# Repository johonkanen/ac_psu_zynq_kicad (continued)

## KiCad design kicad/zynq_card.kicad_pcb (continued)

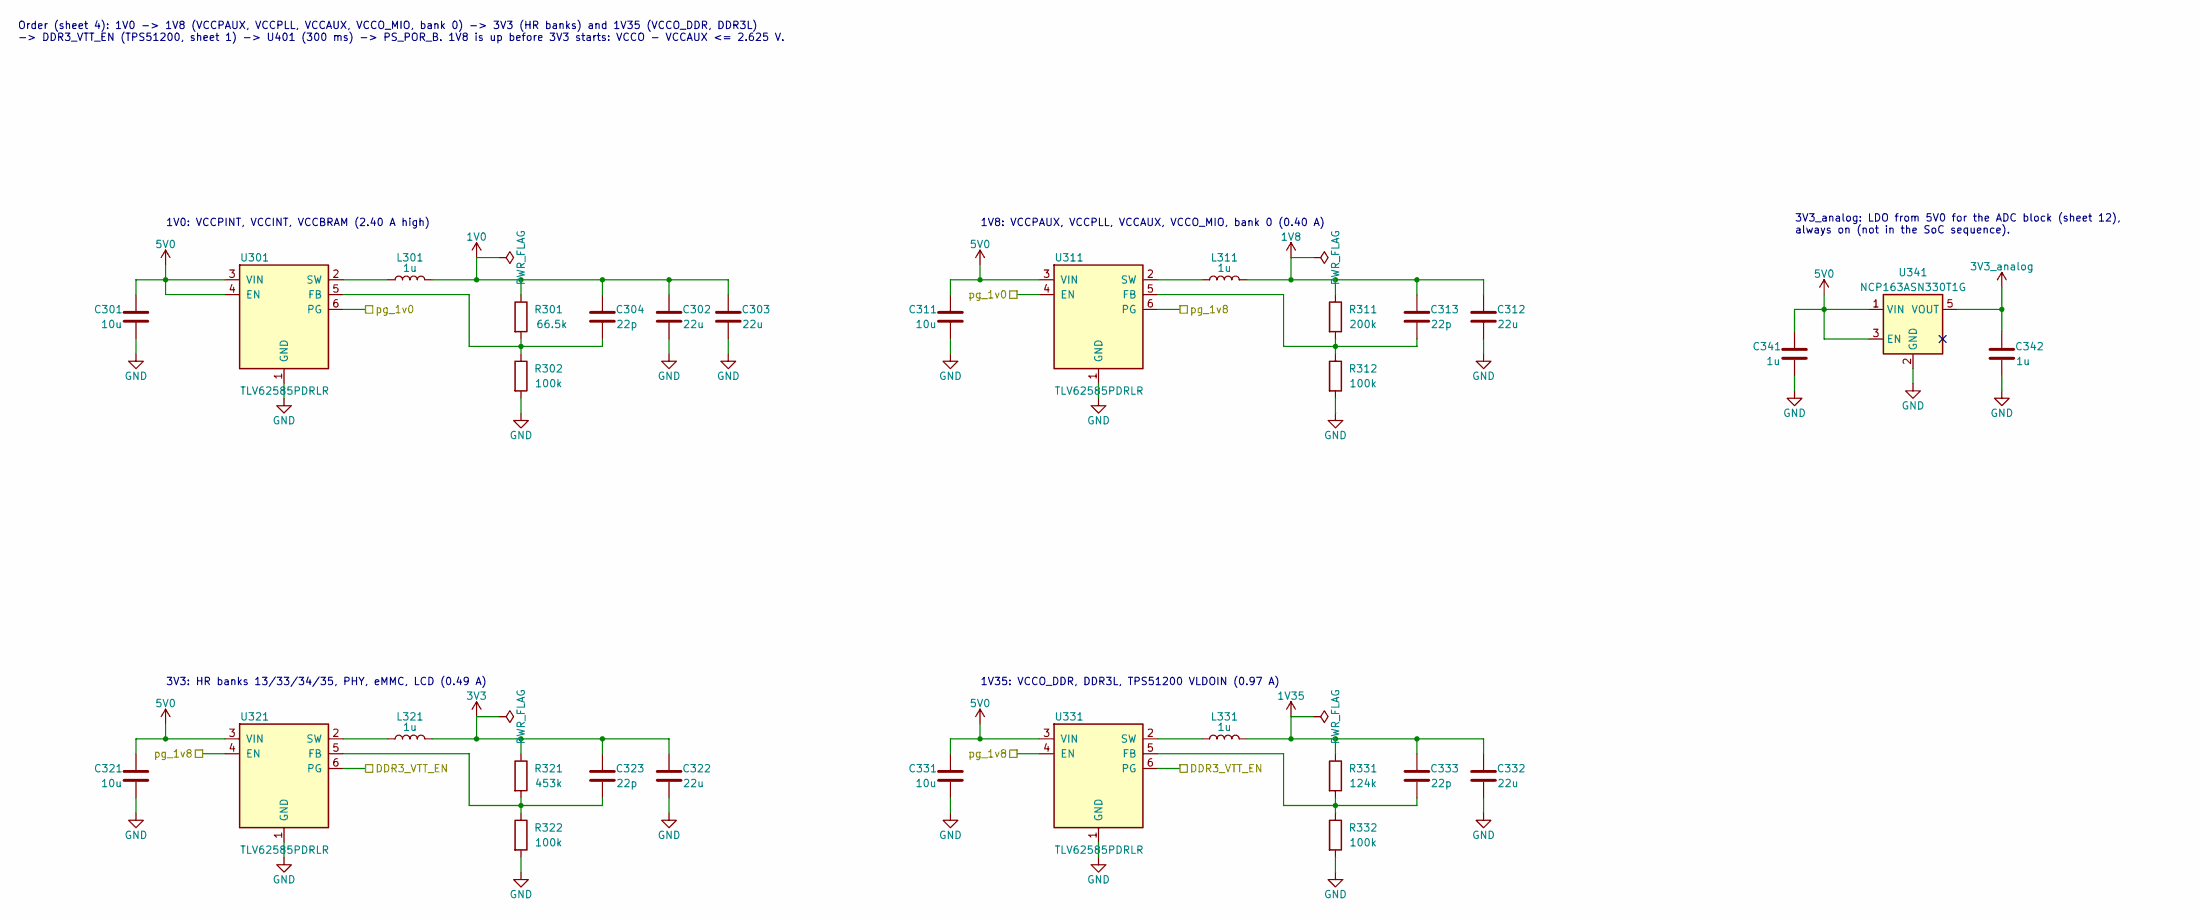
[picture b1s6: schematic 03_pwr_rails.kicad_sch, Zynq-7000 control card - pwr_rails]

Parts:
C301, C311, C321, C331: 10u; C_0805_2012Metric; LCSC C15850
C302, C303, C312, C322, C332: 22u; C_0805_2012Metric; LCSC C45783
C304, C313, C323, C333: 22p; C_0402_1005Metric; LCSC C1555
C341, C342: 1u; C_0402_1005Metric; LCSC C52923
L301, L311, L321, L331: 1u; L_Coilcraft_XxL4020; MPN WPN4020H1R0MT; LCSC C98359
R301: 66.5k; R_0402_1005Metric; LCSC C2998095
R302, R312, R322, R332: 100k; R_0402_1005Metric; LCSC C25741
R311: 200k; R_0402_1005Metric; LCSC C25764
R321: 453k; R_0402_1005Metric; LCSC C27009
R331: 124k; R_0402_1005Metric; LCSC C2933070
U301, U311, U321, U331: TLV62585PDRLR; SOT-563; LCSC C485118
U341: NCP163ASN330T1G; SOT-23-5; LCSC C603656

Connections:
1V0: C302.1, C303.1, C304.1, L301.2, R301.1; also elsewhere on the board
1V8: C312.1, C313.1, L311.2, R311.1; also elsewhere on the board
1V35: C332.1, C333.1, L331.2, R331.1; also elsewhere on the board
3V3: C322.1, C323.1, L321.2, R321.1; also elsewhere on the board
3V3_analog: C342.1, U341.5 (VOUT); also elsewhere on the board
5V0: C301.1, C311.1, C321.1, C331.1, C341.1, U301.3 (VIN), U301.4 (EN), U311.3 (VIN), U321.3 (VIN), U331.3 (VIN), U341.1 (VIN), U341.3 (EN); also elsewhere on the board
/DDR3_VTT_EN: U321.6 (PG), U331.6 (PG); also elsewhere on the board
/pg_1v0: U301.6 (PG), U311.4 (EN); also elsewhere on the board
/pg_1v8: U311.6 (PG), U321.4 (EN), U331.4 (EN); also elsewhere on the board
GND: C301.2, C302.2, C303.2, C311.2, C312.2, C321.2, C322.2, C331.2, C332.2, C341.2, C342.2, R302.2, R312.2, R322.2, R332.2, U301.1 (GND), U311.1 (GND), U321.1 (GND), U331.1 (GND), U341.2 (GND); also elsewhere on the board
unnamed: C304.2, R301.2, R302.1, U301.5 (FB)
unnamed: L301.1, U301.2 (SW)
unnamed: C313.2, R311.2, R312.1, U311.5 (FB)
unnamed: L311.1, U311.2 (SW)
unnamed: C323.2, R321.2, R322.1, U321.5 (FB)
unnamed: L321.1, U321.2 (SW)
unnamed: C333.2, R331.2, R332.1, U331.5 (FB)
unnamed: L331.1, U331.2 (SW)

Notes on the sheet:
Order (sheet 4): 1V0 -> 1V8 (VCCPAUX, VCCPLL, VCCAUX, VCCO_MIO, bank 0) -> 3V3 (HR banks) and 1V35 (VCCO_DDR, DDR3L) -> DDR3_VTT_EN (TPS51200, sheet 1) -> U401 (300 ms) -> PS_POR_B. 1V8 is up before 3V3 starts: VCCO - VCCAUX <= 2.625 V.
1V0: VCCPINT, VCCINT, VCCBRAM (2.40 A high)
1V8: VCCPAUX, VCCPLL, VCCAUX, VCCO_MIO, bank 0 (0.40 A)
3V3: HR banks 13/33/34/35, PHY, eMMC, LCD (0.49 A)
1V35: VCCO_DDR, DDR3L, TPS51200 VLDOIN (0.97 A)
3V3_analog: LDO from 5V0 for the ADC block (sheet 12), always on (not in the SoC sequence).

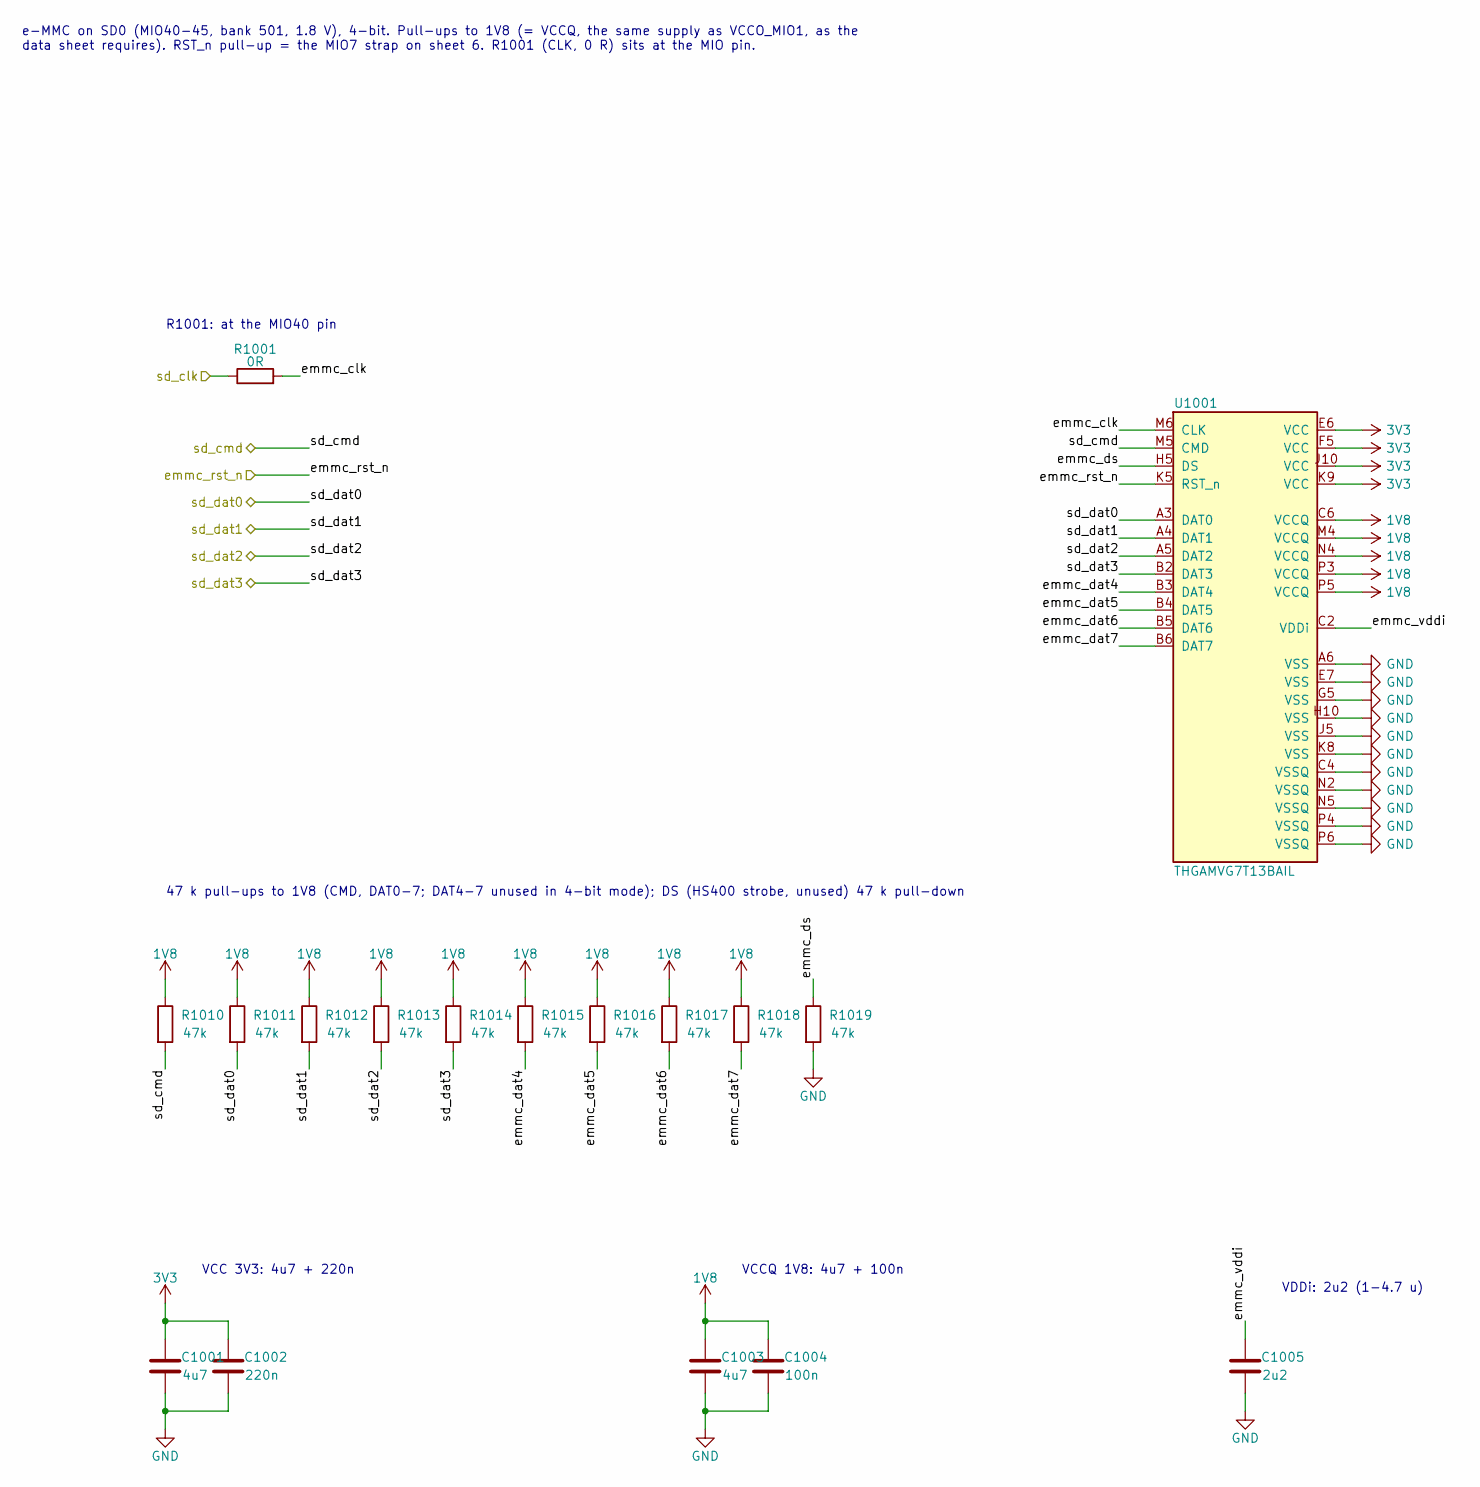
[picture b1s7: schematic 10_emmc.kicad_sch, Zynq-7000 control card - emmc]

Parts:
C1001, C1003: 4u7; C_0402_1005Metric; LCSC C23733
C1002: 220n; C_0402_1005Metric; LCSC C16772
C1004: 100n; C_0402_1005Metric; LCSC C1525
C1005: 2u2; C_0402_1005Metric; LCSC C12530
R1001: 0R; R_0402_1005Metric; LCSC C17168
R1010, R1011, R1012, R1013, R1014, R1015, R1016, R1017, R1018, R1019: 47k; R_0402_1005Metric; LCSC C25792
U1001: THGAMVG7T13BAIL; LFBGA-153_11.5x13mm_Layout14x14_P0.5mm; LCSC C7599693

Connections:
1V8: C1003.1, C1004.1, R1010.1, R1011.1, R1012.1, R1013.1, R1014.1, R1015.1, R1016.1, R1017.1, R1018.1, U1001.C6 (VCCQ), U1001.M4 (VCCQ), U1001.N4 (VCCQ), U1001.P3 (VCCQ), U1001.P5 (VCCQ); also elsewhere on the board
3V3: C1001.1, C1002.1, U1001.E6 (VCC), U1001.F5 (VCC), U1001.J10 (VCC), U1001.K9 (VCC); also elsewhere on the board
/10 emmc/emmc_clk: R1001.2, U1001.M6 (CLK)
/10 emmc/emmc_dat4: R1015.2, U1001.B3 (DAT4)
/10 emmc/emmc_dat5: R1016.2, U1001.B4 (DAT5)
/10 emmc/emmc_dat6: R1017.2, U1001.B5 (DAT6)
/10 emmc/emmc_dat7: R1018.2, U1001.B6 (DAT7)
/10 emmc/emmc_ds: R1019.1, U1001.H5 (DS)
/10 emmc/emmc_vddi: C1005.1, U1001.C2 (VDDi)
/emmc_rst_n: U1001.K5 (RST_n); also elsewhere on the board
/sd_clk: R1001.1; also elsewhere on the board
/sd_cmd: R1010.2, U1001.M5 (CMD); also elsewhere on the board
/sd_dat0: R1011.2, U1001.A3 (DAT0); also elsewhere on the board
/sd_dat1: R1012.2, U1001.A4 (DAT1); also elsewhere on the board
/sd_dat2: R1013.2, U1001.A5 (DAT2); also elsewhere on the board
/sd_dat3: R1014.2, U1001.B2 (DAT3); also elsewhere on the board
GND: C1001.2, C1002.2, C1003.2, C1004.2, C1005.2, R1019.2, U1001.A6 (VSS), U1001.C4 (VSSQ), U1001.E7 (VSS), U1001.G5 (VSS), U1001.H10 (VSS), U1001.J5 (VSS), U1001.K8 (VSS), U1001.N2 (VSSQ), U1001.N5 (VSSQ), U1001.P4 (VSSQ), U1001.P6 (VSSQ); also elsewhere on the board

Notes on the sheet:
e-MMC on SD0 (MIO40-45, bank 501, 1.8 V), 4-bit. Pull-ups to 1V8 (= VCCQ, the same supply as VCCO_MIO1, as the data sheet requires). RST_n pull-up = the MIO7 strap on sheet 6. R1001 (CLK, 0 R) sits at the MIO pin.
R1001: at the MIO40 pin
47 k pull-ups to 1V8 (CMD, DAT0-7; DAT4-7 unused in 4-bit mode); DS (HS400 strobe, unused) 47 k pull-down
VCC 3V3: 4u7 + 220n
VCCQ 1V8: 4u7 + 100n
VDDi: 2u2 (1-4.7 u)

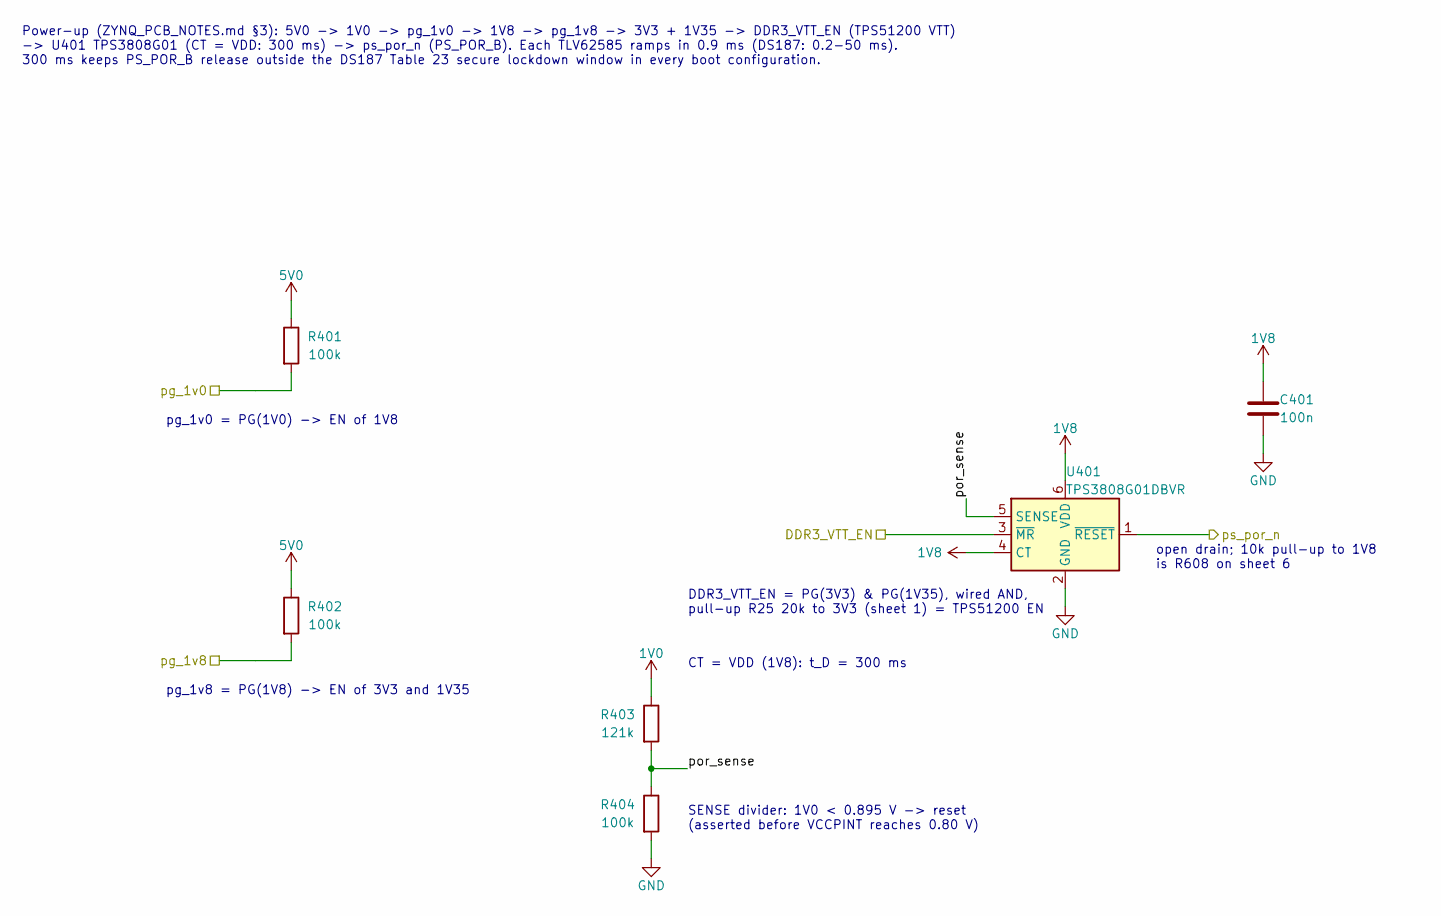
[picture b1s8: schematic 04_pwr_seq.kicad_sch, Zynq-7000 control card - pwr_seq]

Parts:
C401: 100n; C_0402_1005Metric; LCSC C1525
R401, R402, R404: 100k; R_0402_1005Metric; LCSC C25741
R403: 121k; R_0402_1005Metric; LCSC C11693
U401: TPS3808G01DBVR; SOT-23-6; MPN TPS3808G01DBVR; LCSC C19653

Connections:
1V0: R403.1; also elsewhere on the board
1V8: C401.1, U401.4 (CT), U401.6 (VDD); also elsewhere on the board
5V0: R401.1, R402.1; also elsewhere on the board
/04 pwr_seq/por_sense: R403.2, R404.1, U401.5 (SENSE)
/DDR3_VTT_EN: U401.3 (~MR); also elsewhere on the board
/pg_1v0: R401.2; also elsewhere on the board
/pg_1v8: R402.2; also elsewhere on the board
/ps_por_n: U401.1 (~RESET); also elsewhere on the board
GND: C401.2, R404.2, U401.2 (GND); also elsewhere on the board

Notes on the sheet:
Power-up (ZYNQ_PCB_NOTES.md §3): 5V0 -> 1V0 -> pg_1v0 -> 1V8 -> pg_1v8 -> 3V3 + 1V35 -> DDR3_VTT_EN (TPS51200 VTT) -> U401 TPS3808G01 (CT = VDD: 300 ms) -> ps_por_n (PS_POR_B). Each TLV62585 ramps in 0.9 ms (DS187: 0.2-50 ms). 300 ms keeps PS_POR_B release outside the DS187 Table 23 secure lockdown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
pg_1v0 = PG(1V0) -> EN of 1V8
pg_1v8 = PG(1V8) -> EN of 3V3 and 1V35
DDR3_VTT_EN = PG(3V3) & PG(1V35), wired AND, pull-up R25 20k to 3V3 (sheet 1) = TPS51200 EN
CT = VDD (1V8): t_D = 300 ms
SENSE divider: 1V0 < 0.895 V -> reset (asserted before VCCPINT reaches 0.80 V)
open drain; 10k pull-up to 1V8 is R608 on sheet 6

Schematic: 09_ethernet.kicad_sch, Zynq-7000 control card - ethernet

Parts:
C901, C921, C922, C931, C932, C933, C934, C936, C941, C950, C951: 100n; C_0402_1005Metric; LCSC C1525
C910, C911: 27p; C_0402_1005Metric; LCSC C107002
C920: 10u; C_0805_2012Metric; LCSC C15850
C930, C935, C940: 1u; C_0402_1005Metric; LCSC C52923
FB901: BLM15PX121SN1D; L_0402_1005Metric; LCSC C88970
J9: HR911130A; RJ45_Hanrun_HR911130A_Horizontal; LCSC C54408
R901, R902, R903, R904, R905, R906, R907, R908, R909, R910, R911, R912: 22R; R_0402_1005Metric; LCSC C25092
R920, R921, R922, R923, R924, R925, R926, R927, R928, R929, R930: 4k7; R_0402_1005Metric; LCSC C25900
R931: 2.49k 1%; R_0402_1005Metric; LCSC C25884
R932: 10k; R_0402_1005Metric; LCSC C25744
R933: 1k; R_0402_1005Metric; LCSC C11702
R950: 330R; R_0402_1005Metric; LCSC C25104
U901: RTL8211FDI-CG; QFN-40-1EP_5x5mm_P0.4mm_EP3.6x3.6mm_ThermalVias; LCSC C692886
U902: 74LVC1G07GW; SOT-353_SC-70-5; LCSC C282345
Y901: 25MHz; Crystal_SMD_3225-4Pin_3.2x2.5mm; MPN X322525MRB4SI; LCSC C70593

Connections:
1V8: C951.1, R929.1, R930.1, U902.5 (VCC); also elsewhere on the board
3V3: C940.1, C941.1, FB901.1, R928.1, R932.1, R950.1, U901.29 (DVDD33); also elsewhere on the board
/09 ethernet/eth_ct: C950.1, J9.1 (TCT)
/09 ethernet/eth_led_a: J9.11 (LEDG_A), R950.2
/09 ethernet/eth_led_k: J9.12 (LEDG_K), R928.2, U901.34 (LED2/CFG_LDO1)
/09 ethernet/eth_mdi_a_N: J9.3 (MDI0-), U901.2 (MDIN0)
/09 ethernet/eth_mdi_a_P: J9.2 (MDI0+), U901.1 (MDIP0)
/09 ethernet/eth_mdi_b_N: J9.7 (MDI1-), U901.5 (MDIN1)
/09 ethernet/eth_mdi_b_P: J9.4 (MDI1+), U901.4 (MDIP1)
/09 ethernet/eth_mdi_c_N: J9.6 (MDI2-), U901.7 (MDIN2)
/09 ethernet/eth_mdi_c_P: J9.5 (MDI2+), U901.6 (MDIP2)
/09 ethernet/eth_mdi_d_N: J9.9 (MDI3-), U901.10 (MDIN3)
/09 ethernet/eth_mdi_d_P: J9.8 (MDI3+), U901.9 (MDIP3)
/09 ethernet/phy_avdd33: C920.1, C921.1, C922.1, FB901.2, U901.11 (AVDD33), U901.40 (AVDD33)
/09 ethernet/phy_dvdd_rg: C935.1, C936.1, R920.1, R925.1, U901.28 (DVDD_RG)
/09 ethernet/phy_led0: R926.1, U901.32 (LED0/CFG_EXT)
/09 ethernet/phy_led1: R927.1, U901.33 (LED1/CFG_LDO0)
/09 ethernet/phy_rset: R931.1, U901.39 (RSET)
/09 ethernet/phy_rstb: C901.1, R932.2, U901.12 (PHYRSTB), U902.4
/09 ethernet/phy_rx_ctl: R908.2, R922.1, U901.26 (RXCTL/PHYAD2)
/09 ethernet/phy_rxc: R907.2, R921.1, U901.27 (RXC/PHYAD1)
/09 ethernet/phy_rxd0: R909.2, R925.2, U901.25 (RXD0/RXDLY)
/09 ethernet/phy_rxd1: R910.2, R924.1, U901.24 (RXD1/TXDLY)
/09 ethernet/phy_rxd2: R911.2, R923.1, U901.23 (RXD2/PLLOFF)
/09 ethernet/phy_rxd3: R912.2, R920.2, U901.22 (RXD3/PHYAD0)
/09 ethernet/phy_tx_ctl: R902.2, U901.19 (TXCTL)
/09 ethernet/phy_txc: R901.2, U901.20 (TXC)
/09 ethernet/phy_txd0: R903.2, U901.18 (TXD0)
/09 ethernet/phy_txd1: R904.2, U901.17 (TXD1)
/09 ethernet/phy_txd2: R905.2, U901.16 (TXD2)
/09 ethernet/phy_txd3: R906.2, U901.15 (TXD3)
/09 ethernet/phy_vdd10: C930.1, C931.1, C932.1, C933.1, C934.1, U901.3 (AVDD10), U901.8 (AVDD10), U901.21 (DVDD10), U901.30 (LDO_OUT), U901.38 (AVDD10)
/09 ethernet/phy_xi: C910.1, U901.36 (XTAL_IN), Y901.1
/09 ethernet/phy_xo: C911.1, U901.37 (XTAL_OUT), Y901.3
/eth_int_n: R930.2, U901.31 (INTB/PMEB); also elsewhere on the board
/eth_rst_n: R933.1, U902.2; also elsewhere on the board
/mdc: U901.13 (MDC); also elsewhere on the board
/mdio: R929.2, U901.14 (MDIO); also elsewhere on the board
/rgmii_rx_ctl: R908.1; also elsewhere on the board
/rgmii_rxc: R907.1; also elsewhere on the board
/rgmii_rxd0: R909.1; also elsewhere on the board
/rgmii_rxd1: R910.1; also elsewhere on the board
/rgmii_rxd2: R911.1; also elsewhere on the board
/rgmii_rxd3: R912.1; also elsewhere on the board
/rgmii_tx_ctl: R902.1; also elsewhere on the board
/rgmii_txc: R901.1; also elsewhere on the board
/rgmii_txd0: R903.1; also elsewhere on the board
/rgmii_txd1: R904.1; also elsewhere on the board
/rgmii_txd2: R905.1; also elsewhere on the board
/rgmii_txd3: R906.1; also elsewhere on the board
GND: C901.2, C910.2, C911.2, C920.2, C921.2, C922.2, C930.2, C931.2, C932.2, C933.2, C934.2, C935.2, C936.2, C940.2, C941.2, C950.2, C951.2, J9.10 (CHS), J9.SH (SHIELD), R921.2, R922.2, R923.2, R924.2, R926.2, R927.2, R931.2, R933.2, U901.41 (GND), U902.3 (GND), Y901.2 (G), Y901.4 (G); also elsewhere on the board

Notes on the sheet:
RTL8211FDI-CG gigabit PHY, RGMII at 1.8 V (internal pad LDO) to GEM0 (MIO16-27, bank 501), MDIO0 on MIO52/53, PHY address 1. 3.3 V only: core 1.0 V from its own LDO. J9 = HanRun HR911130A magjack (green LED from LED2, yellow spare), placed per MECHANICAL.md.
RGMII series 22 R: TX at the SoC (MIO), RX at the PHY (source side)
Straps 4k7: PHYAD = 001 (RXD3 up, RXC/RXCTL down), PLLOFF/TXDLY = 0, RXDLY = 1 (RX pins to DVDD_RG); CFG_EXT = 0 (LED0 down), CFG_LDO = 10 (LED1 down, LED2 up to 3V3) -> 1.8 V RGMII pads. MDIO/INT_N pull-ups to 1V8.
PHYRSTB is a 3.3 V input: U902 74LVC1G07 (1V8 supply) open drain, R932 10k to 3V3, C901 filter. R933 1k holds eth_rst_n (MIO9) low against the MIO reset pull-up until software releases the PHY.
25 MHz crystal 3225, 27 p load (Agilex card values), +/-50 ppm total; place at the PHY
AVDD33 (pins 11, 40) through a ferrite: 10u + 2 x 100n
LDO_OUT 1.0 V -> AVDD10 (3, 8, 38) + DVDD10 (21) only: 1u + 4 x 100n (>= 0.1u, Table 9.2)
DVDD_RG: RGMII pad LDO output (1.8 V), caps only
DVDD33 (pin 29)
Jack LED: green anode via R950 to 3V3, cathode on PHY LED2 (3.3 V pin, active low with its CFG_LDO1 pull-up R928). Program LCR for link/activity.

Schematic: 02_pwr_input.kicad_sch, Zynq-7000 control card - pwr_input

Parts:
C201: 47u; C_1206_3216Metric; LCSC C96123
C202: 22u; C_0805_2012Metric; LCSC C45783
C203: 100n; C_0402_1005Metric; LCSC C1525
J6: 2x3 1.27mm (bottom); PinSocket_2x03_P1.27mm_Vertical

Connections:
5V0: C201.1, C202.1, C203.1, J6.2, J6.4, J6.6; also elsewhere on the board
GND: C201.2, C202.2, C203.2, J6.1, J6.3, J6.5; also elsewhere on the board

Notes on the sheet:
J6 = baseboard J12 (2x3 1.27 mm socket on B.Cu, MECHANICAL.md): 5V0 = baseboard 5V_ISOL, GND = ISOGND. Supply budget: POWER_BUDGET.md (0.89 A typ / 1.44 A high; needs the baseboard U8 upgrade to 1.5-2 A).
GND: the card's only ground (baseboard ISOGND)
Input bulk at J6 (the regulators have their own 10u).

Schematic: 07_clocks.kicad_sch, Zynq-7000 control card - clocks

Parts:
C701: 470n; C_0402_1005Metric; LCSC C47339
FB701: BLM18PG121SN1D; L_0603_1608Metric; MPN BLM18PG121SN1D; LCSC C14709
R701: 33; R_0402_1005Metric; LCSC C25105
Y701: 33.333MHz; Oscillator_SMD_Abracon_ASE-4Pin_3.2x2.5mm; MPN OT322533.3333MJBA4SL; LCSC C2831392

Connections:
1V8: FB701.1; also elsewhere on the board
/07 clocks/osc_vdd: C701.1, FB701.2, Y701.1 (EN), Y701.4 (Vdd)
/ps_clk: R701.2; also elsewhere on the board
GND: C701.2, Y701.2 (GND); also elsewhere on the board
unnamed: R701.1, Y701.3 (OUT)

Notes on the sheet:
PS_CLK: Y701 33.333 MHz, 1.8 V CMOS (bank 500 = VCCO_MIO0 = 1.8 V) -> R701 33 R at Y701 -> ps_clk (U20 F7). Circuit of the Agilex 3 card's oscillator: EN tied to VDD, supply through FB701 with C701 470 n. Layout: Y701 close to F7, one point-to-point trace, R701 at the oscillator pin.

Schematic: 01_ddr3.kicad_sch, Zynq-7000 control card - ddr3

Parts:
C93, C98, C105, C106, C109, C110: .01uF; C_0402_1005Metric; MPN CL05B103KB5NNNC; LCSC C15195
C94, C95, C96, C97, C131: .1uF; C_0402_1005Metric; MPN CL05B104KO5NNNC; LCSC C1525
C99: 100uF; C_1210_3225Metric; MPN CL32A107MQVNNNE; LCSC C49066
C100, C127: 4.7uF; C_0402_1005Metric; MPN CL05A475MP5NRNC; LCSC C23733
C101, C102, C103, C104: .47uF; C_0402_1005Metric; MPN CL05A474KP5NNNC; LCSC C47339
C125, C126, C128, C129, C130: 10uF; C_0603_1608Metric; MPN CL10A106KP8NNNC; LCSC C19702
D7: BLUE LED; C_0603_1608Metric; MPN VLMB1300-GS08; LCSC C435849
R25: 20k; R_0402_1005Metric; MPN RT0402BRD0720KL; LCSC C705630
R46, R49: 240 1%; R_0402_1005Metric; MPN RC0402FR-07240RL; LCSC C114755
R47, R48: 10k 1%; R_0402_1005Metric; MPN 0402WGF1002TCE; LCSC C25744
R50, R75, R76: 80.6 1%; R_0402_1005Metric; MPN RC0402FR-0780R6L; LCSC C185392
R51, R52, R53, R54, R55, R56, R57, R58, R59, R60, R61, R62, R63, R64, R65, R66, R67, R68, R69, R70, R71, R72, R73: 40.2 1%; R_0402_1005Metric; MPN RC0402FR-0740R2L; LCSC C274892
R74: 4.7k; R_0402_1005Metric; MPN 0402WGF4701TCE; LCSC C25900
R101: 100k; R_0402_1005Metric; MPN 0402WGF1003TCE; LCSC C25741
R102: 150; R_0402_1005Metric; MPN RC-02K1500FT; LCSC C140202
U8: TPS51200DRCR; VSON-10-1EP_3x3mm_P0.5mm_EP1.65x2.4mm_ThermalVias; MPN TPS51200DRCR; LCSC C34771
U15, U16: MT41K256M16TW-107:P; FBGA-96-DDR3-SDRAM; MPN MT41K256M16TW-107:P; LCSC C253882
U20: XC7Z020-2CLG484I; BGA-484_19.0x19.0mm_Layout22x22_P0.80mm_dia0.40mm; MPN XC7Z020-2CLG484I; LCSC C157624

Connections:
1V35: C94.1, C96.1, C99.1, C100.1, C101.1, C102.1, C103.1, C104.1, C109.1, C110.1, C125.1, C126.1, R47.1, R75.2, U8.2 (VLDOIN), U15.A1 (VDDQ), U15.A8 (VDDQ), U15.B2 (VDD), U15.C1 (VDDQ), U15.C9 (VDDQ), U15.D2 (VDDQ), U15.D9 (VDD), U15.E9 (VDDQ), U15.F1 (VDDQ), U15.G7 (VDD), U15.H2 (VDDQ), U15.H9 (VDDQ), U15.K2 (VDD), U15.K8 (VDD), U15.N1 (VDD), U15.N9 (VDD), U15.R1 (VDD), U15.R9 (VDD), U16.A1 (VDDQ), U16.A8 (VDDQ), U16.B2 (VDD), U16.C1 (VDDQ), U16.C9 (VDDQ), U16.D2 (VDDQ), U16.D9 (VDD), U16.E9 (VDDQ), U16.F1 (VDDQ), U16.G7 (VDD), U16.H2 (VDDQ), U16.H9 (VDDQ), U16.K2 (VDD), U16.K8 (VDD), U16.N1 (VDD), U16.N9 (VDD), U16.R1 (VDD), U16.R9 (VDD), U20.E2 (VCCO_DDR_502[9]), U20.F5 (VCCO_DDR_502[9]), U20.H1 (VCCO_DDR_502[9]), U20.J4 (VCCO_DDR_502[9]), U20.K7 (VCCO_DDR_502[9]), U20.M3 (VCCO_DDR_502[9]), U20.N6 (VCCO_DDR_502[9]), U20.R2 (VCCO_DDR_502[9]), U20.V1 (VCCO_DDR_502[9]); also elsewhere on the board
3V3: C127.2, R25.1, R101.1, R102.2, U8.10 (VIN); also elsewhere on the board
/01 ddr3/PGOOD_LED: D7.2 (A), R102.1
/01 ddr3/VREF: C93.1, C94.2, C95.1, C96.2, C97.1, C98.1, C105.1, C106.1, R47.2, R48.1, U8.1 (REFIN), U15.H1 (VREFDQ), U15.M8 (VREFCA), U16.H1 (VREFDQ), U16.M8 (VREFCA), U20.H7 (PS_DDR_VREF0_502), U20.P7 (PS_DDR_VREF1_502)
/01 ddr3/ZQH: R46.1, U15.L8 (ZQ)
/01 ddr3/ZQL: R49.1, U16.L8 (ZQ)
/DDR3_VTT_EN: R25.2, U8.7 (EN); also elsewhere on the board
DDR3_A0: R51.1, U15.N3 (A0), U16.N3 (A0), U20.M4 (PS_DDR_A0_502)
DDR3_A1: R52.1, U15.P7 (A1), U16.P7 (A1), U20.M5 (PS_DDR_A1_502)
DDR3_A2: R53.1, U15.P3 (A2), U16.P3 (A2), U20.K4 (PS_DDR_A2_502)
DDR3_A3: R54.1, U15.N2 (A3), U16.N2 (A3), U20.L4 (PS_DDR_A3_502)
DDR3_A4: R55.1, U15.P8 (A4), U16.P8 (A4), U20.K6 (PS_DDR_A4_502)
DDR3_A5: R56.1, U15.P2 (A5), U16.P2 (A5), U20.K5 (PS_DDR_A5_502)
DDR3_A6: R57.1, U15.R8 (A6), U16.R8 (A6), U20.J7 (PS_DDR_A6_502)
DDR3_A7: R58.1, U15.R2 (A7), U16.R2 (A7), U20.J6 (PS_DDR_A7_502)
DDR3_A8: R59.1, U15.T8 (A8), U16.T8 (A8), U20.J5 (PS_DDR_A8_502)
DDR3_A9: R60.1, U15.R3 (A9), U16.R3 (A9), U20.H5 (PS_DDR_A9_502)
DDR3_A10: R61.1, U15.L7 (A10/AP), U16.L7 (A10/AP), U20.J3 (PS_DDR_A10_502)
DDR3_A11: R62.1, U15.R7 (A11), U16.R7 (A11), U20.G5 (PS_DDR_A11_502)
DDR3_A12: R63.1, U15.N7 (A12/!BC), U16.N7 (A12/!BC), U20.H4 (PS_DDR_A12_502)
DDR3_A13: R64.1, U15.T3 (A13), U16.T3 (A13), U20.F4 (PS_DDR_A13_502)
DDR3_A14: R65.1, U15.T7 (A14), U16.T7 (A14), U20.G4 (PS_DDR_A14_502)
DDR3_BA0: R66.1, U15.M2 (BA0), U16.M2 (BA0), U20.L7 (PS_DDR_BA0_502)
DDR3_BA1: R67.1, U15.N8 (BA1), U16.N8 (BA1), U20.L6 (PS_DDR_BA1_502)
DDR3_BA2: R68.1, U15.M3 (BA2), U16.M3 (BA2), U20.M6 (PS_DDR_BA2_502)
DDR3_CAS#: R70.1, U15.K3 (~CAS), U16.K3 (~CAS), U20.P3 (PS_DDR_CAS_B_502)
DDR3_CKE: U15.K9 (CKE), U16.K9 (CKE), U20.V3 (PS_DDR_CKE_502)
DDR3_CK_N: R50.2, U15.K7 (~CK), U16.K7 (~CK), U20.N5 (PS_DDR_CKN_502)
DDR3_CK_P: R50.1, U15.J7 (CK), U16.J7 (CK), U20.N4 (PS_DDR_CKP_502)
DDR3_CS#: R73.1, U15.L2 (~CS), U16.L2 (~CS), U20.P6 (PS_DDR_CS_B_502)
DDR3_DM0: U16.E7 (LDM), U20.B1 (PS_DDR_DM0_502)
DDR3_DM1: U16.D3 (UDM), U20.H3 (PS_DDR_DM1_502)
DDR3_DM2: U15.E7 (LDM), U20.P1 (PS_DDR_DM2_502)
DDR3_DM3: U15.D3 (UDM), U20.AA2 (PS_DDR_DM3_502)
DDR3_DQ0: U16.E3 (DQ0), U20.C3 (PS_DDR_DQ1_502)
DDR3_DQ1: U16.F7 (DQ1), U20.F2 (PS_DDR_DQ6_502)
DDR3_DQ2: U16.F2 (DQ2), U20.B2 (PS_DDR_DQ2_502)
DDR3_DQ3: U16.F8 (DQ3), U20.F1 (PS_DDR_DQ7_502)
DDR3_DQ4: U16.H3 (DQ4), U20.E3 (PS_DDR_DQ4_502)
DDR3_DQ5: U16.H8 (DQ5), U20.E1 (PS_DDR_DQ5_502)
DDR3_DQ6: U16.G2 (DQ6), U20.D3 (PS_DDR_DQ3_502)
DDR3_DQ7: U16.H7 (DQ7), U20.D1 (PS_DDR_DQ0_502)
DDR3_DQ8: U16.D7 (DQ8), U20.L3 (PS_DDR_DQ12_502)
DDR3_DQ9: U16.C3 (DQ9), U20.L1 (PS_DDR_DQ10_502)
DDR3_DQ10: U16.C8 (DQ10), U20.L2 (PS_DDR_DQ11_502)
DDR3_DQ11: U16.C2 (DQ11), U20.J1 (PS_DDR_DQ14_502)
DDR3_DQ12: U16.A7 (DQ12), U20.K1 (PS_DDR_DQ13_502)
DDR3_DQ13: U16.A2 (DQ13), U20.G2 (PS_DDR_DQ8_502)
DDR3_DQ14: U16.B8 (DQ14), U20.K3 (PS_DDR_DQ15_502)
DDR3_DQ15: U16.A3 (DQ15), U20.G1 (PS_DDR_DQ9_502)
DDR3_DQ16: U15.E3 (DQ0), U20.T3 (PS_DDR_DQ17_502)
DDR3_DQ17: U15.F7 (DQ1), U20.T1 (PS_DDR_DQ19_502)
DDR3_DQ18: U15.F2 (DQ2), U20.M1 (PS_DDR_DQ16_502)
DDR3_DQ19: U15.F8 (DQ3), U20.T2 (PS_DDR_DQ21_502)
DDR3_DQ20: U15.H3 (DQ4), U20.M2 (PS_DDR_DQ22_502)
DDR3_DQ21: U15.H8 (DQ5), U20.R1 (PS_DDR_DQ23_502)
DDR3_DQ22: U15.G2 (DQ6), U20.N3 (PS_DDR_DQ18_502)
DDR3_DQ23: U15.H7 (DQ7), U20.R3 (PS_DDR_DQ20_502)
DDR3_DQ24: U15.D7 (DQ8), U20.AA3 (PS_DDR_DQ24_502)
DDR3_DQ25: U15.C3 (DQ9), U20.Y1 (PS_DDR_DQ31_502)
DDR3_DQ26: U15.C8 (DQ10), U20.Y3 (PS_DDR_DQ29_502)
DDR3_DQ27: U15.C2 (DQ11), U20.W1 (PS_DDR_DQ28_502)
DDR3_DQ28: U15.A7 (DQ12), U20.AA1 (PS_DDR_DQ26_502)
DDR3_DQ29: U15.A2 (DQ13), U20.U1 (PS_DDR_DQ25_502)
DDR3_DQ30: U15.B8 (DQ14), U20.W3 (PS_DDR_DQ30_502)
DDR3_DQ31: U15.A3 (DQ15), U20.U2 (PS_DDR_DQ27_502)
DDR3_DQS0_N: U16.G3 (~LDQS), U20.D2 (PS_DDR_DQS_N0_502)
DDR3_DQS0_P: U16.F3 (LDQS), U20.C2 (PS_DDR_DQS_P0_502)
DDR3_DQS1_N: U16.B7 (~UDQS), U20.J2 (PS_DDR_DQS_N1_502)
DDR3_DQS1_P: U16.C7 (UDQS), U20.H2 (PS_DDR_DQS_P1_502)
DDR3_DQS2_N: U15.G3 (~LDQS), U20.P2 (PS_DDR_DQS_N2_502)
DDR3_DQS2_P: U15.F3 (LDQS), U20.N2 (PS_DDR_DQS_P2_502)
DDR3_DQS3_N: U15.B7 (~UDQS), U20.W2 (PS_DDR_DQS_N3_502)
DDR3_DQS3_P: U15.C7 (UDQS), U20.V2 (PS_DDR_DQS_P3_502)
DDR3_DRST#: R74.1, U15.T2 (~RESET), U16.T2 (~RESET), U20.F3 (PS_DDR_DRST_B_502)
DDR3_ODT: R72.1, U15.K1 (ODT), U16.K1 (ODT), U20.P5 (PS_DDR_ODT_502)
DDR3_RAS#: R69.1, U15.J3 (~RAS), U16.J3 (~RAS), U20.R5 (PS_DDR_RAS_B_502)
DDR3_VTT: C128.1, C129.1, C130.1, R51.2, R52.2, R53.2, R54.2, R55.2, R56.2, R57.2, R58.2, R59.2, R60.2, R61.2, R62.2, R63.2, R64.2, R65.2, R66.2, R67.2, R68.2, R69.2, R70.2, R71.2, R72.2, R73.2, U8.3 (VO), U8.5 (VOSNS)
DDR3_WE#: R71.1, U15.L3 (~WE), U16.L3 (~WE), U20.R4 (PS_DDR_WE_B_502)
GND: C93.2, C95.2, C97.2, C98.2, C99.2, C100.2, C101.2, C102.2, C103.2, C104.2, C105.2, C106.2, C109.2, C110.2, C125.2, C126.2, C127.1, C128.2, C129.2, C130.2, C131.2, R46.2, R48.2, R49.2, R74.2, R76.2, U8.4 (PGND), U8.8 (GND), U8.11, U15.A9 (VSS), U15.B1 (VSSQ), U15.B3 (VSS), U15.B9 (VSSQ), U15.D1 (VSSQ), U15.D8 (VSSQ), U15.E1 (VSS), U15.E2 (VSSQ), U15.E8 (VSSQ), U15.F9 (VSSQ), U15.G1 (VSSQ), U15.G8 (VSS), U15.G9 (VSSQ), U15.J2 (VSS), U15.J8 (VSS), U15.M1 (VSS), U15.M9 (VSS), U15.P1 (VSS), U15.P9 (VSS), U15.T1 (VSS), U15.T9 (VSS), U16.A9 (VSS), U16.B1 (VSSQ), U16.B3 (VSS), U16.B9 (VSSQ), U16.D1 (VSSQ), U16.D8 (VSSQ), U16.E1 (VSS), U16.E2 (VSSQ), U16.E8 (VSSQ), U16.F9 (VSSQ), U16.G1 (VSSQ), U16.G8 (VSS), U16.G9 (VSSQ), U16.J2 (VSS), U16.J8 (VSS), U16.M1 (VSS), U16.M9 (VSS), U16.P1 (VSS), U16.P9 (VSS), U16.T1 (VSS), U16.T9 (VSS); also elsewhere on the board
unnamed: D7.1 (K), R101.2, U8.9 (PGOOD)
unnamed: C131.1, U8.6 (REFOUT)
unnamed: R75.1, U20.M7 (PS_DDR_VRN_502)
unnamed: R76.1, U20.N7 (PS_DDR_VRP_502)

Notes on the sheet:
Differential termination at end / first break This is the only P-to-N termination in ZC702 DDR3
Terminations as described in UG933 and shown in ZC702 schematic
Pinout identical to TW 96-ball FBGA variant
RECOMMENDED: Fly-by and point-to-point routing is recommended for optimal memory performance
DDR3L trace impedance: 40ohm differential 80ohm single
1066 Mb/s (533 MHz) Should be attainable by all speed grades of Zynq through the PS DDR interface This precludes use of internal Vref
DDR3
DDR3 block from juliancoy/zynqPCB (MIT, NOTICE), imported by tools/sheets/01_ddr3.py from DDR3.sch. References and DDR3_* names are the source's. Changes: REUSE_LOG.md E3 (DDR3_VTT_EN is a sheet port, driven by our power sequencing), E4 (U15/U16 MT41K256M16TW-107:P). Do not edit by hand.

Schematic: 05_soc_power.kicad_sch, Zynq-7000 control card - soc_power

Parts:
C4, C8, C14, C15, C17, C18, C23, C29, C30, C31, C34: .47uF; C_0402_1005Metric; MPN CL05A474KP5NNNC; LCSC C47339
C5, C9, C19, C20, C24: 4.7uF; C_0402_1005Metric; MPN CL05A475MP5NRNC; LCSC C23733
C11, C26, C33: 10uF; C_0603_1608Metric; MPN CL10A106KP8NNNC; LCSC C19702
C28: 100uF; C_1210_3225Metric; MPN CL32A107MQVNNNE; LCSC C49066
C46, C47, C50, C55, C65, C116, C117, C118, C119, C121: .47uF; C_0402_1005Metric; LCSC C47339
C57, C59, C114, C122: 4.7uF; C_0402_1005Metric; LCSC C23733
C61: 47uF; C_0805_2012Metric; LCSC C16780
C67: 22uF; C_1206_3216Metric; MPN CL31A226KAHNNNE; LCSC C12891
C501: 330u; CP_EIA-7343-31_Kemet-D; MPN T520D337M006ATE015; LCSC C116744
C502, C508, C509, C510: 100u; C_1210_3225Metric; LCSC C49066
C503, C504, C516, C517, C518, C522, C523, C524: 4u7; C_0402_1005Metric; LCSC C23733
C505, C506, C507, C513, C514, C515, C519, C520, C521, C525, C526, C527, C529: 470n; C_0402_1005Metric; LCSC C47339
C511, C512: 47u; C_1210_3225Metric; LCSC C77101
C528: 10u; C_0603_1608Metric; LCSC C19702
FB1: 0; C_0603_1608Metric; MPN 0603WAF0000T5E; LCSC C21189
FB501: BLM18SG121TN1D; L_0603_1608Metric; LCSC C113030
U20: XC7Z020-2CLG484I; BGA-484_19.0x19.0mm_Layout22x22_P0.80mm_dia0.40mm; MPN XC7Z020-2CLG484I; LCSC C157624

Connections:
1V0: C8.1, C9.1, C11.1, C23.1, C24.1, C28.1, C29.1, C30.1, C31.1, C501.1, C502.1, C503.1, C504.1, C505.1, C506.1, C507.1, U20.G8 (VCCPINT[6]), U20.H9 (VCCPINT[6]), U20.H11 (VCCBRAM[2]), U20.J8 (VCCPINT[6]), U20.J10 (VCCBRAM[2]), U20.J12 (VCCINT[8]), U20.J14 (VCCINT[8]), U20.K13 (VCCINT[8]), U20.L8 (VCCPINT[6]), U20.L14 (VCCINT[8]), U20.M13 (VCCINT[8]), U20.N8 (VCCPINT[6]), U20.N14 (VCCINT[8]), U20.P13 (VCCINT[8]), U20.R8 (VCCPINT[6]), U20.R14 (VCCINT[8]); also elsewhere on the board
1V8: C4.1, C5.1, C14.1, C15.1, C17.1, C18.1, C19.1, C20.1, C26.1, C59.1, C122.1, C508.1, C509.1, C510.1, C511.1, C512.1, FB1.2, FB501.1, U20.K9 (VCCPAUX[4]), U20.M9 (VCCPAUX[4]), U20.P9 (VCCPAUX[4]), U20.T9 (VCCPAUX[4]); also elsewhere on the board
1V35: C513.1, C514.1, C515.1; also elsewhere on the board
3V3: C46.1, C47.1, C50.1, C55.1, C57.1, C61.1, C65.1, C67.1, C114.1, C116.1, C117.1, C118.1, C119.1, C121.1, C516.1, C517.1, C518.1, C519.1, C520.1, C521.1, C522.1, C523.1, C524.1, C525.1, C526.1, C527.1; also elsewhere on the board
/05 soc_power/VCCAUX: C33.1, C34.1, FB1.1, U20.L10 (VCCAUX[4]), U20.N10 (VCCAUX[4]), U20.P11 (VCCAUX[4]), U20.R10 (VCCAUX[4])
/05 soc_power/VCCPLL: C528.1, C529.1, FB501.2, U20.H10 (VCCPLL)
GND: C4.2, C5.2, C8.2, C9.2, C11.2, C14.2, C15.2, C17.2, C18.2, C19.2, C20.2, C23.2, C24.2, C26.2, C28.2, C29.2, C30.2, C31.2, C33.2, C34.2, C46.2, C47.2, C50.2, C55.2, C57.2, C59.2, C61.2, C65.2, C67.2, C114.2, C116.2, C117.2, C118.2, C119.2, C121.2, C122.2, C501.2, C502.2, C503.2, C504.2, C505.2, C506.2, C507.2, C508.2, C509.2, C510.2, C511.2, C512.2, C513.2, C514.2, C515.2, C516.2, C517.2, C518.2, C519.2, C520.2, C521.2, C522.2, C523.2, C524.2, C525.2, C526.2, C527.2, C528.2, C529.2, U20.A5 (GND[63]), U20.A15 (GND[63]), U20.AA5 (GND[63]), U20.AA15 (GND[63]), U20.AB8 (GND[63]), U20.AB18 (GND[63]), U20.B8 (GND[63]), U20.B18 (GND[63]), U20.C1 (GND[63]), U20.C11 (GND[63]), U20.C21 (GND[63]), U20.D4 (GND[63]), U20.D14 (GND[63]), U20.E7 (GND[63]), U20.E17 (GND[63]), U20.F10 (GND[63]), U20.F20 (GND[63]), U20.G3 (GND[63]), U20.H6 (GND[63]), U20.H8 (GND[63]), U20.H12 (GND[63]), U20.H14 (GND[63]), U20.H16 (GND[63]), U20.J9 (GND[63]), U20.J11 (GND[63]), U20.J13 (GND[63]), U20.J19 (GND[63]), U20.K2 (GND[63]), U20.K8 (GND[63]), U20.K10 (GND[63]), U20.K14 (GND[63]), U20.K22 (GND[63]), U20.L5 (GND[63]), U20.L9 (GND[63]), U20.L13 (GND[63]), U20.L15 (GND[63]), U20.M8 (GND[63]), U20.M10 (GND[63]), U20.M14 (GND[63]), U20.M18 (GND[63]), U20.N1 (GND[63]), U20.N9 (GND[63]), U20.N13 (GND[63]), U20.N21 (GND[63]), U20.P4 (GND[63]), U20.P8 (GND[63]), U20.P10 (GND[63]), U20.P12 (GND[63]), U20.P14 (GND[63]), U20.R9 (GND[63]), U20.R11 (GND[63]), U20.R13 (GND[63]), U20.R17 (GND[63]), U20.T20 (GND[63]), U20.U3 (GND[63]), U20.U13 (GND[63]), U20.V6 (GND[63]), U20.V16 (GND[63]), U20.W9 (GND[63]), U20.W19 (GND[63]), U20.Y2 (GND[63]), U20.Y12 (GND[63]), U20.Y22 (GND[63]); also elsewhere on the board

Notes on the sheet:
U20 unit 9 and the SoC decoupling. Left/bottom: juliancoy/zynqPCB power.sch (MIT, NOTICE), converted by tools/sheets/05_soc_power.py: only the decaps in the block copper, source refs and positions. Do not edit by hand. Changes: REUSE_LOG.md E5 (VCCPLL through FB501, FB1 = 0 ohm), E6 (C59/C122 on 1V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
UG933 count, block + C5xx: 1V0 (VCCINT+VCCBRAM+VCCPINT): 330u 1, 100u 2, 4u7 4, 470n 8 block C28 100u, C9 C24 4u7, C8 C23 C29 C30 C31 470n (+ C11 10u) 1V8 (VCCAUX+VCCPAUX+MIO0+MIO1+VCCO_0): 100u 3, 47u 2, 4u7 4, 470n 5 block C5 C19 C20 C59 C122 4u7, C4 C14 C15 C17 C18 C34 470n (+ C26 C33 10u) VCCPL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
1V0: VCCINT/VCCBRAM/VCCPINT bulk and the missing mid/high-frequency caps
1V8: VCCPAUX, MIO0, MIO1 100u; VCCAUX, VCCO_0 47u
1V35 VCCO_DDR: 3 more 470n at bank 502
3V3 VCCO_34 (no caps in the block)
3V3 VCCO_35 (no caps in the block)
Block 3V3 caps under U20 (juliancoy's other sheets, source refs): banks 13/33
Block, E6: MIO1 (E12), MIO0 (C6)
E5: VCCPLL from 1V8 through a 120R bead (UG933 Fig. 5-2: BLM18SG121TN1D, GRM188R60J106ME47, GRM155R60J474KE19). Planelet >= 2 mm wide, < 76 mm long, C528 to the H10 via; C529 within 5.1 mm of trace from the H10/GND vias. Replaces juliancoy's direct +1V8.

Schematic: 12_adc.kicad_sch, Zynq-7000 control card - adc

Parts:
C1201, C1206: 1u; C_0402_1005Metric; LCSC C52923
C1202: 680p C0G; C_0402_1005Metric; LCSC C113781
C1203, C1205: 100n; C_0402_1005Metric; LCSC C1525
C1204: 4u7; C_0603_1608Metric; LCSC C19666
R1201: 100R; R_0402_1005Metric; LCSC C25076
R1202, R1203, R1204, R1205: 1k; R_0402_1005Metric; LCSC C11702
R1206, R1210, R1211, R1212: 33R; R_0402_1005Metric; LCSC C25105
U1201: SN74LV4051APWR; TSSOP-16_4.4x5mm_P0.65mm; LCSC C7793
U1202: OPA365AIDBVR; SOT-23-5; LCSC C96626
U1203: ADS7056IRUGR; ads7056; LCSC C2669798

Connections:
1V0: R1201.1; also elsewhere on the board
1V8: R1202.1; also elsewhere on the board
1V35: R1204.1; also elsewhere on the board
3V3: C1206.1, R1203.1, U1203.4 (DVDD); also elsewhere on the board
3V3_analog: C1201.1, C1203.1, C1204.1, C1205.1, U1201.16 (VDD), U1202.5 (V+), U1203.6 (AVDD); also elsewhere on the board
/12 adc/adc_ainp: C1202.1, R1206.2, U1203.7 (AINP)
/12 adc/adc_cs_n_r: R1210.2, U1203.1 (~CS)
/12 adc/adc_mux_out: U1201.3 (X), U1202.3 (+)
/12 adc/adc_sclk_r: R1211.2, U1203.3 (SCLK)
/12 adc/adc_sdo_r: R1212.2, U1203.2 (SDO)
/12 adc/mon_1v0: R1201.2, U1201.14 (X1)
/12 adc/mon_1v8: R1202.2, U1201.15 (X2)
/12 adc/mon_1v35: R1204.2, U1201.5 (X5)
/12 adc/mon_3v3: R1203.2, R1205.1, U1201.12 (X3)
/adbsel0: U1201.11 (A); also elsewhere on the board
/adbsel1: U1201.10 (B); also elsewhere on the board
/adbsel2: U1201.9 (C); also elsewhere on the board
/adc_cs_n: R1210.1; also elsewhere on the board
/adc_sclk: R1211.1; also elsewhere on the board
/adc_sdo: R1212.1; also elsewhere on the board
/isoada1: U1201.4 (X7); also elsewhere on the board
/isoada2: U1201.1 (X4); also elsewhere on the board
/isoada3: U1201.2 (X6); also elsewhere on the board
GND: C1201.2, C1202.2, C1203.2, C1204.2, C1205.2, C1206.2, R1205.2, U1201.6 (INH), U1201.7 (VEE), U1201.8 (VSS), U1201.13 (X0), U1202.2 (V-), U1203.5 (GND), U1203.8 (AINM); also elsewhere on the board
unnamed: R1206.1, U1202.1, U1202.4 (-)

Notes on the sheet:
ADC chain: mux U1201 -> buffer U1202 -> ADS7056 U1203 (Ti135 sheet 13; front end as on the Agilex 3 card, 2.5 MSPS). Mux: X0 GND (zero ref), X1 1V0, X2 1V8, X3 3V3/2, X4 isoada2, X5 1V35, X6 isoada3, X7 isoada1. Full scale 0..3.3 V (AVDD = reference, 3V3_analog). DVDD on 3V3: SPI and selects straig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
U1201 VCC
SN74LV4051A (SCLS428K): pins 7/8 GND; VIH 2.31 V at 3.3 V
Rail monitors
3V3 via 1k/1k divider
U1202 V+
AVDD = reference: 4u7 0603 + 100n at the pin
DVDD 3V3
SPI series 33 R (60 MHz SCLK); DVDD 3V3 = bank 33
